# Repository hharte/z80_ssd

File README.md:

# z80_ssd: Z-80 Solid-State Drive

## Introduction

This project implements a solid-state disk controller for the Z80.  The board plugs into the Z80 CPU socket and the Z80 CPU plugs into the board.  A [Microchip PIC18F47Q43](https://www.microchip.com/en-us/product/PIC18F47Q43) microcontroller implements the controller and SD Memory card interface using SPI.

While the z80_ssd could implement almost any hard disk controller that uses I/O ports for data transfer, the particular controller implemented mimics the IBC/Integrated Business Computers MCC Hard Disk Controller.

The original controller supports four ST-506 drives.  Drive 0 is the boot drive, and Drive 3 is a 5- or 10MB removable cartridge drive.  The other two drives were unused in the standard [IBC MultiStar](https://github.com/hharte/integrated-business-computers/tree/master/MultiStar) computer.

## Architecture

### I/O Access Handling

The z80_ssd piggybacks on the Z80 CPU socket to gain access to all of the Z80 CPU’s signals.  The PIC18F47Q43 was chosen because it has a relatively large amount of RAM (8K) and FLASH (128K.)  To minimize the number of components required, and to facilitate maximum flexibility, the MCU’s Configurable Logic Cells (CLCs) are used:

CLC1 - Decodes CPU_A[7:4] to allow the z80_ssd to respond to a block of 16 I/O addresses.  The current design uses one 4-input AND gate to decode address 40h-4Fh, like the original disk controller.  There are three spare 4-input AND gates in CLC1, so the design could be expanded to decode up to four blocks of 16 I/O ports if desired.

This schematic diagram illustrates three address ranges decoded by the z80_ssd: 40h-4Fh, 0C0h-0CFh, 0D0h-0DFh.

CLC2 - Uses the output of CLC1 along with CPU_M1# and CPU_IORQ# to set a flip-flop when the requested I/O access is performed by the CPU.  The output of this flip-flop pulls down the CPU_WAIT# pin via an open-collector output from the MCU.  CLC2 generates an interrupt to the MCU, and MCU then processes the I/O read or write.  After the MCU finishes processing the I/O access, it de-asserts WAIT# by resetting the flip-flop in CLC2.

CLC3 - Although not strictly required, the z80_ssd employs a 74ABTH245 bus transceiver for the CPU data bus to ensure proper timing.  The MCU’s CLC3 drives the bus transceiver’s output enable.

Due to the piggyback nature of the z80_ssd, it is fabricated on a 0.4mm thick PCB, and uses a machined Mill-Max long-pin DIP socket.  To raise the z80_ssd above other components on the computer’s motherboard, the long-pin DIP is plugged into a stamped 40-pin DIP socket which is then inserted into the original Z80 CPU socket.

### SD Memory Card

The SD memory card is connected to the MCU’s SPI interface.  It uses the [FatFs library](http://elm-chan.org/fsw/ff/00index_e.html) and Microchip’s SD-SPI library.  The activity LED on the z80_ssd is driven by the SD memory card’s CS# pin.

The SPI clock runs at 8MHz, and is in polled mode.  It may be possible to increase the throughput by using interrupt-driven DMA mode, but I have not tried that.

Running OASIS 5.6, a 16MB disk partition can be verified (read) in 3 minutes, 35 seconds.  While the I/O interface is much slower than the hardware-driven FIFO of the original disk controller design, the overall performance feels about the same: solid-state disks do not have seek or rotational latency overhead, which makes these aspects of the disk faster than the original.

```
>HDPERF

>SHOW TIME
05:33:00 Friday, October 22, 1993

>VERIFY S

Cylinder: 132 Head: 14

>SHOW TIME
05:36:33 Friday, October 22, 1993

D(8) Label: "REMOVBKU",
     Archived from disk "HOWARD1 " on 10/23/83 14:13,
     Capacity: 9,744K bytes (609-2-32),
     Available: 0K bytes (0%),
     Largest area: 0K bytes,
     1 file in use (out of 16).

S(3) Label: "HOWARD1 ",
     Archived to disk "REMOVBKU" on 10/23/83 14:13,
     Capacity: 15,960K bytes (133-15-32),
     Available: 14,884K bytes (93%),
     Largest area: 14,879K bytes,
     188 files in use (out of 1,944).
```

### Debugging Facilities

The z80_ssd includes a 5V TTL UART for console I/O as well as a standard Microchip ICSP port on a 1x6 0.1” header.

Jumper JP1 can be removed to block CPU_WAIT# from being asserted.  This can be useful for debugging.  JP1 should be installed for normal operation.

## Other Uses

The z80_ssd hardware and MCU can be used to implement other types of I/O devices or different kinds of disk controllers.  One thing to be aware of is that **_no other hardware in the system should drive the bus when the z80_ssd registers are accessed_**.  For use in an S-100 bus system, additional logic would be needed to prevent the bus drivers on the S-100 board from driving against the z80_ssd.  In the IBC MultiStar machine where I use the z80_ssd, I had to disable the on-board ST-506 controller.  This was accomplished by removing the PAL that does the address decoding for the disk controller, tying one of the inputs inactive, and then placing the PAL back into the system.

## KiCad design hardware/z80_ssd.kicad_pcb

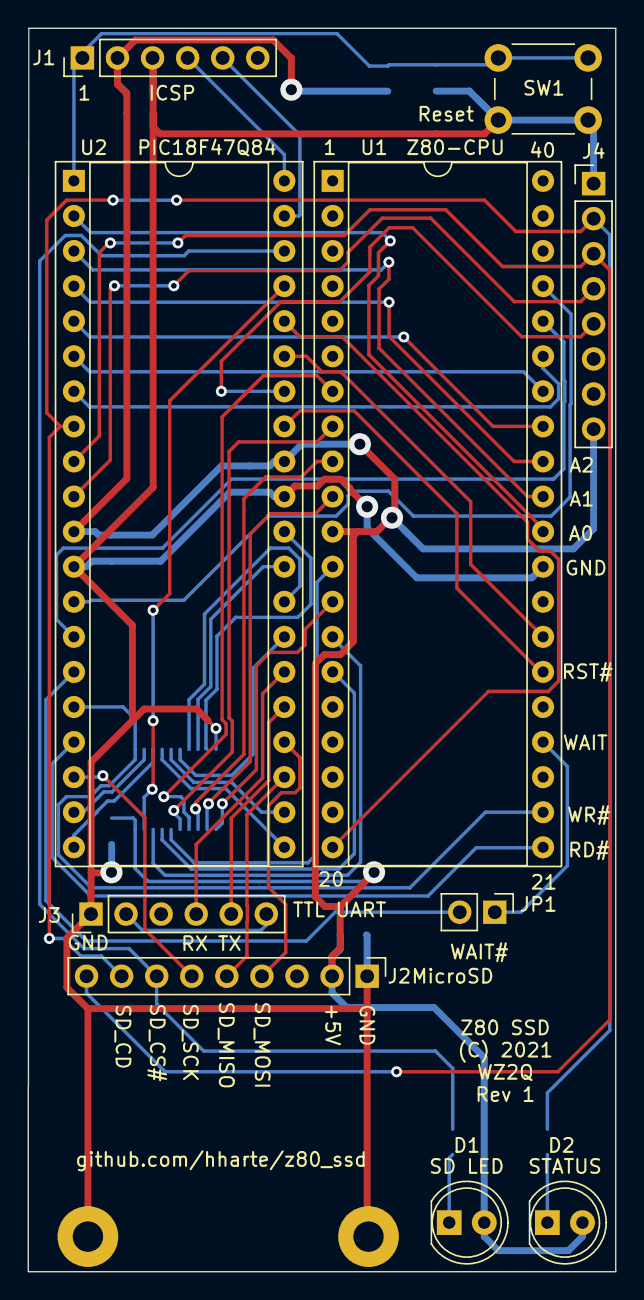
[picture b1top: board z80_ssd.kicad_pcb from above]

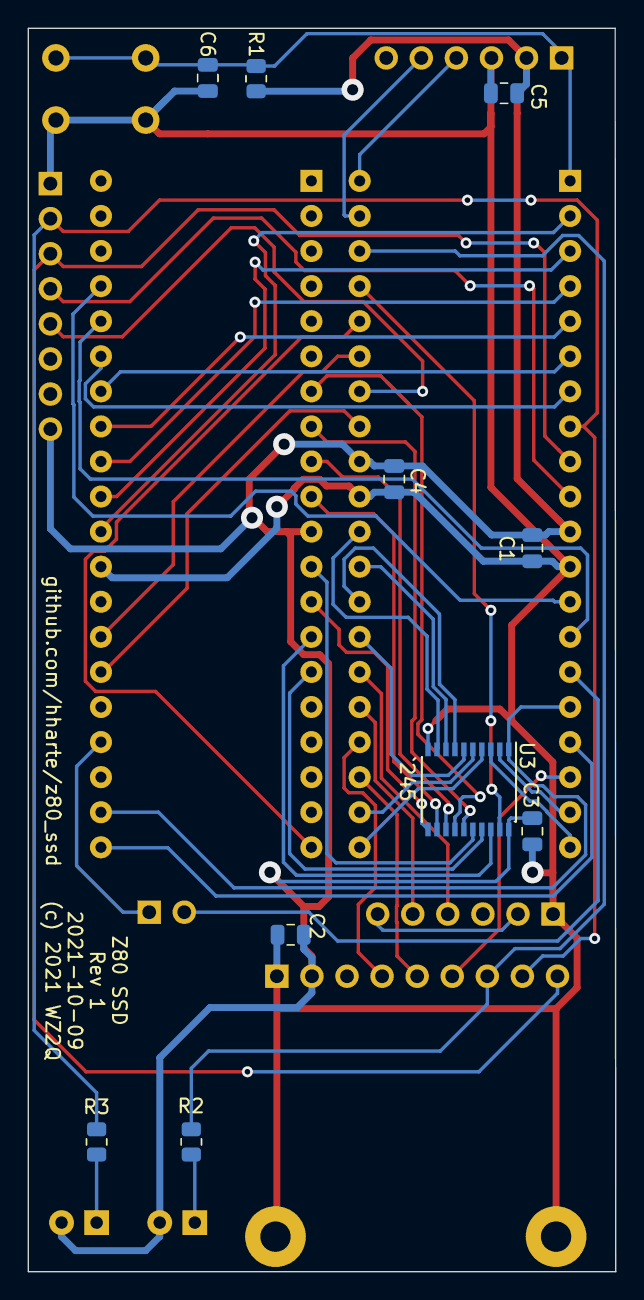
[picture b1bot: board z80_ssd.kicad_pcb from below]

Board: 2 copper layers, 42.5 x 90.0 mm, 22 parts (10 on the bottom side), 50 nets.

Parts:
C1, C2, C3, C4, C5: 0.1uF; C_0805_2012Metric
C6: 0.01uF; C_0805_2012Metric
D1, D2: LED; LED_D5.0mm
H1, H2: MountingHole_Pad; MountingHole_2.2mm_M2_Pad
J1, J3: Conn_01x06_Male; PinHeader_1x06_P2.54mm_Vertical
J2: Pololu-2587_MicroSD; PinHeader_1x09_P2.54mm_Vertical
J4: Conn_01x08_Male; PinHeader_1x08_P2.54mm_Vertical
JP1: Jumper; PinHeader_1x02_P2.54mm_Vertical
R1: 10K; R_0805_2012Metric
R2, R3: 470; R_0805_2012Metric
SW1: SW_Push; SW_PUSH_6mm
U1: Z80CPU; DIP-40_W15.24mm_Socket
U2: PIC18F47Q84; DIP-40_W15.24mm_Socket
U3: 74HC245; SSOP-20_4.4x6.5mm_P0.65mm

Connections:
+5V: C1.1, C2.1, C3.1, C4.1, C5.1, D1.2, D2.2, J1.2, J2.2, J4.8, R1.1, U1.11, U2.11, U2.32, U3.20
/CPU_A0: U1.30, U2.2
/CPU_A1: U1.31, U2.3
/CPU_A2: U1.32, U2.4
/CPU_A3: U1.33, U2.5
/CPU_A4: U1.34, U2.6
/CPU_A5: U1.35, U2.7
/CPU_A6: U1.36, U2.14
/CPU_A7: U1.37, U2.13
/CPU_D0: U1.14, U3.18
/CPU_D1: U1.15, U3.17
/CPU_D2: U1.12, U3.16
/CPU_D3: U1.8, U3.15
/CPU_D4: U1.7, U3.14
/CPU_D5: U1.9, U3.13
/CPU_D6: U1.10, U3.12
/CPU_D7: U1.13, U3.11
/CPU_D_CE#: U2.37, U3.19
/CPU_IORQ#: U1.20, U2.36
/CPU_M1#: U1.27, U2.35
/CPU_RD#: U1.21, U2.17
/CPU_RESET#: U1.26, U2.33
/CPU_WAIT#: JP1.1, U1.24
/CPU_WR#: U1.22, U2.16, U3.1
/ICSP_PGC: J1.5, U2.39
/MCLR#: C6.1, J1.1, R1.2, SW1.1, U2.1
/MCU_D0: U2.19, U3.2
/MCU_D1: U2.20, U3.3
/MCU_D2: U2.21, U3.4
/MCU_D3: U2.22, U3.5
/MCU_D4: U2.27, U3.6
/MCU_D5: U2.28, U3.7
/MCU_D6: U2.29, U3.8
/MCU_D7: U2.30, U3.9
/MCU_RB1: J4.5, U2.34
/MCU_RE0: J2.8, J4.2, R3.2, U2.8
/MCU_RE1: J2.9, J4.3, U2.9
/MCU_RE2: J4.4, U2.10
/MCU_WAIT#: JP1.2, U2.15
/SD_CS#: J2.7, R2.2, U2.38
/SD_MISO: J2.5, U2.23
/SD_MOSI: J2.4, U2.24
/SD_SCK: J2.6, U2.18
/UART_RX: J3.4, U2.26
/UART_TX: J3.5, U2.25
GND: C1.2, C2.2, C3.2, C4.2, C5.2, C6.2, H1.1, H2.1, J1.3, J2.1, J3.1, J4.1, SW1.2, U1.29, U2.12, U2.31, U3.10
unnamed: D1.1, R2.1
unnamed: D2.1, R3.1
unnamed: J1.4, U2.40
unnamed: J3.2, J3.6

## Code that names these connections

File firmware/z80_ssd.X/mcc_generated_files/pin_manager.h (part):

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// get/set CPU_A0 aliases
#define CPU_A0_TRIS                 TRISAbits.TRISA0
#define CPU_A0_LAT                  LATAbits.LATA0
#define CPU_A0_PORT                 PORTAbits.RA0
#define CPU_A0_WPU                  WPUAbits.WPUA0
#define CPU_A0_OD                   ODCONAbits.ODCA0
#define CPU_A0_ANS                  ANSELAbits.ANSELA0
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// get/set CPU_A1 aliases
#define CPU_A1_TRIS                 TRISAbits.TRISA1
#define CPU_A1_LAT                  LATAbits.LATA1
#define CPU_A1_PORT                 PORTAbits.RA1
#define CPU_A1_WPU                  WPUAbits.WPUA1
#define CPU_A1_OD                   ODCONAbits.ODCA1
#define CPU_A1_ANS                  ANSELAbits.ANSELA1
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// get/set CPU_A2 aliases
#define CPU_A2_TRIS                 TRISAbits.TRISA2
#define CPU_A2_LAT                  LATAbits.LATA2
#define CPU_A2_PORT                 PORTAbits.RA2
#define CPU_A2_WPU                  WPUAbits.WPUA2
#define CPU_A2_OD                   ODCONAbits.ODCA2
#define CPU_A2_ANS                  ANSELAbits.ANSELA2
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// get/set CPU_A3 aliases
#define CPU_A3_TRIS                 TRISAbits.TRISA3
#define CPU_A3_LAT                  LATAbits.LATA3
#define CPU_A3_PORT                 PORTAbits.RA3
#define CPU_A3_WPU                  WPUAbits.WPUA3
#define CPU_A3_OD                   ODCONAbits.ODCA3
#define CPU_A3_ANS                  ANSELAbits.ANSELA3
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// get/set UART_TX aliases
#define UART_TX_TRIS                 TRISCbits.TRISC7
#define UART_TX_LAT                  LATCbits.LATC7
#define UART_TX_PORT                 PORTCbits.RC7
#define UART_TX_WPU                  WPUCbits.WPUC7
#define UART_TX_OD                   ODCONCbits.ODCC7
#define UART_TX_ANS                  ANSELCbits.ANSELC7
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// get/set CPU_D0 aliases
#define CPU_D0_TRIS                 TRISDbits.TRISD0
#define CPU_D0_LAT                  LATDbits.LATD0
#define CPU_D0_PORT                 PORTDbits.RD0
#define CPU_D0_WPU                  WPUDbits.WPUD0
#define CPU_D0_OD                   ODCONDbits.ODCD0
#define CPU_D0_ANS                  ANSELDbits.ANSELD0
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// get/set CPU_D1 aliases
#define CPU_D1_TRIS                 TRISDbits.TRISD1
#define CPU_D1_LAT                  LATDbits.LATD1
#define CPU_D1_PORT                 PORTDbits.RD1
#define CPU_D1_WPU                  WPUDbits.WPUD1
#define CPU_D1_OD                   ODCONDbits.ODCD1
#define CPU_D1_ANS                  ANSELDbits.ANSELD1
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// get/set CPU_D2 aliases
#define CPU_D2_TRIS                 TRISDbits.TRISD2
#define CPU_D2_LAT                  LATDbits.LATD2
#define CPU_D2_PORT                 PORTDbits.RD2
#define CPU_D2_WPU                  WPUDbits.WPUD2
#define CPU_D2_OD                   ODCONDbits.ODCD2
#define CPU_D2_ANS                  ANSELDbits.ANSELD2
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// get/set CPU_D3 aliases
#define CPU_D3_TRIS                 TRISDbits.TRISD3
#define CPU_D3_LAT                  LATDbits.LATD3
#define CPU_D3_PORT                 PORTDbits.RD3
#define CPU_D3_WPU                  WPUDbits.WPUD3
#define CPU_D3_OD                   ODCONDbits.ODCD3
#define CPU_D3_ANS                  ANSELDbits.ANSELD3
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// get/set CPU_D4 aliases
#define CPU_D4_TRIS                 TRISDbits.TRISD4
#define CPU_D4_LAT                  LATDbits.LATD4
#define CPU_D4_PORT                 PORTDbits.RD4
#define CPU_D4_WPU                  WPUDbits.WPUD4
#define CPU_D4_OD                   ODCONDbits.ODCD4
#define CPU_D4_ANS                  ANSELDbits.ANSELD4
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// get/set CPU_D5 aliases
#define CPU_D5_TRIS                 TRISDbits.TRISD5
#define CPU_D5_LAT                  LATDbits.LATD5
#define CPU_D5_PORT                 PORTDbits.RD5
#define CPU_D5_WPU                  WPUDbits.WPUD5
#define CPU_D5_OD                   ODCONDbits.ODCD5
#define CPU_D5_ANS                  ANSELDbits.ANSELD5
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// get/set CPU_D6 aliases
#define CPU_D6_TRIS                 TRISDbits.TRISD6
#define CPU_D6_LAT                  LATDbits.LATD6
#define CPU_D6_PORT                 PORTDbits.RD6
#define CPU_D6_WPU                  WPUDbits.WPUD6
#define CPU_D6_OD                   ODCONDbits.ODCD6
#define CPU_D6_ANS                  ANSELDbits.ANSELD6
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// get/set CPU_D7 aliases
#define CPU_D7_TRIS                 TRISDbits.TRISD7
#define CPU_D7_LAT                  LATDbits.LATD7
#define CPU_D7_PORT                 PORTDbits.RD7
#define CPU_D7_WPU                  WPUDbits.WPUD7
#define CPU_D7_OD                   ODCONDbits.ODCD7
#define CPU_D7_ANS                  ANSELDbits.ANSELD7
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
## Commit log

2021-10-24 Initial commit: Boots OASIS 5.6 on the IBC MultiStar.

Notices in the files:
firmware/z80_ssd.X/mcc_generated_files/pin_manager.h:
(c) 2018 Microchip Technology Inc. and its subsidiaries.
hardware/z80_ssd.kicad_pcb:
(C) 2021
(c) 2021 WZ2Q
